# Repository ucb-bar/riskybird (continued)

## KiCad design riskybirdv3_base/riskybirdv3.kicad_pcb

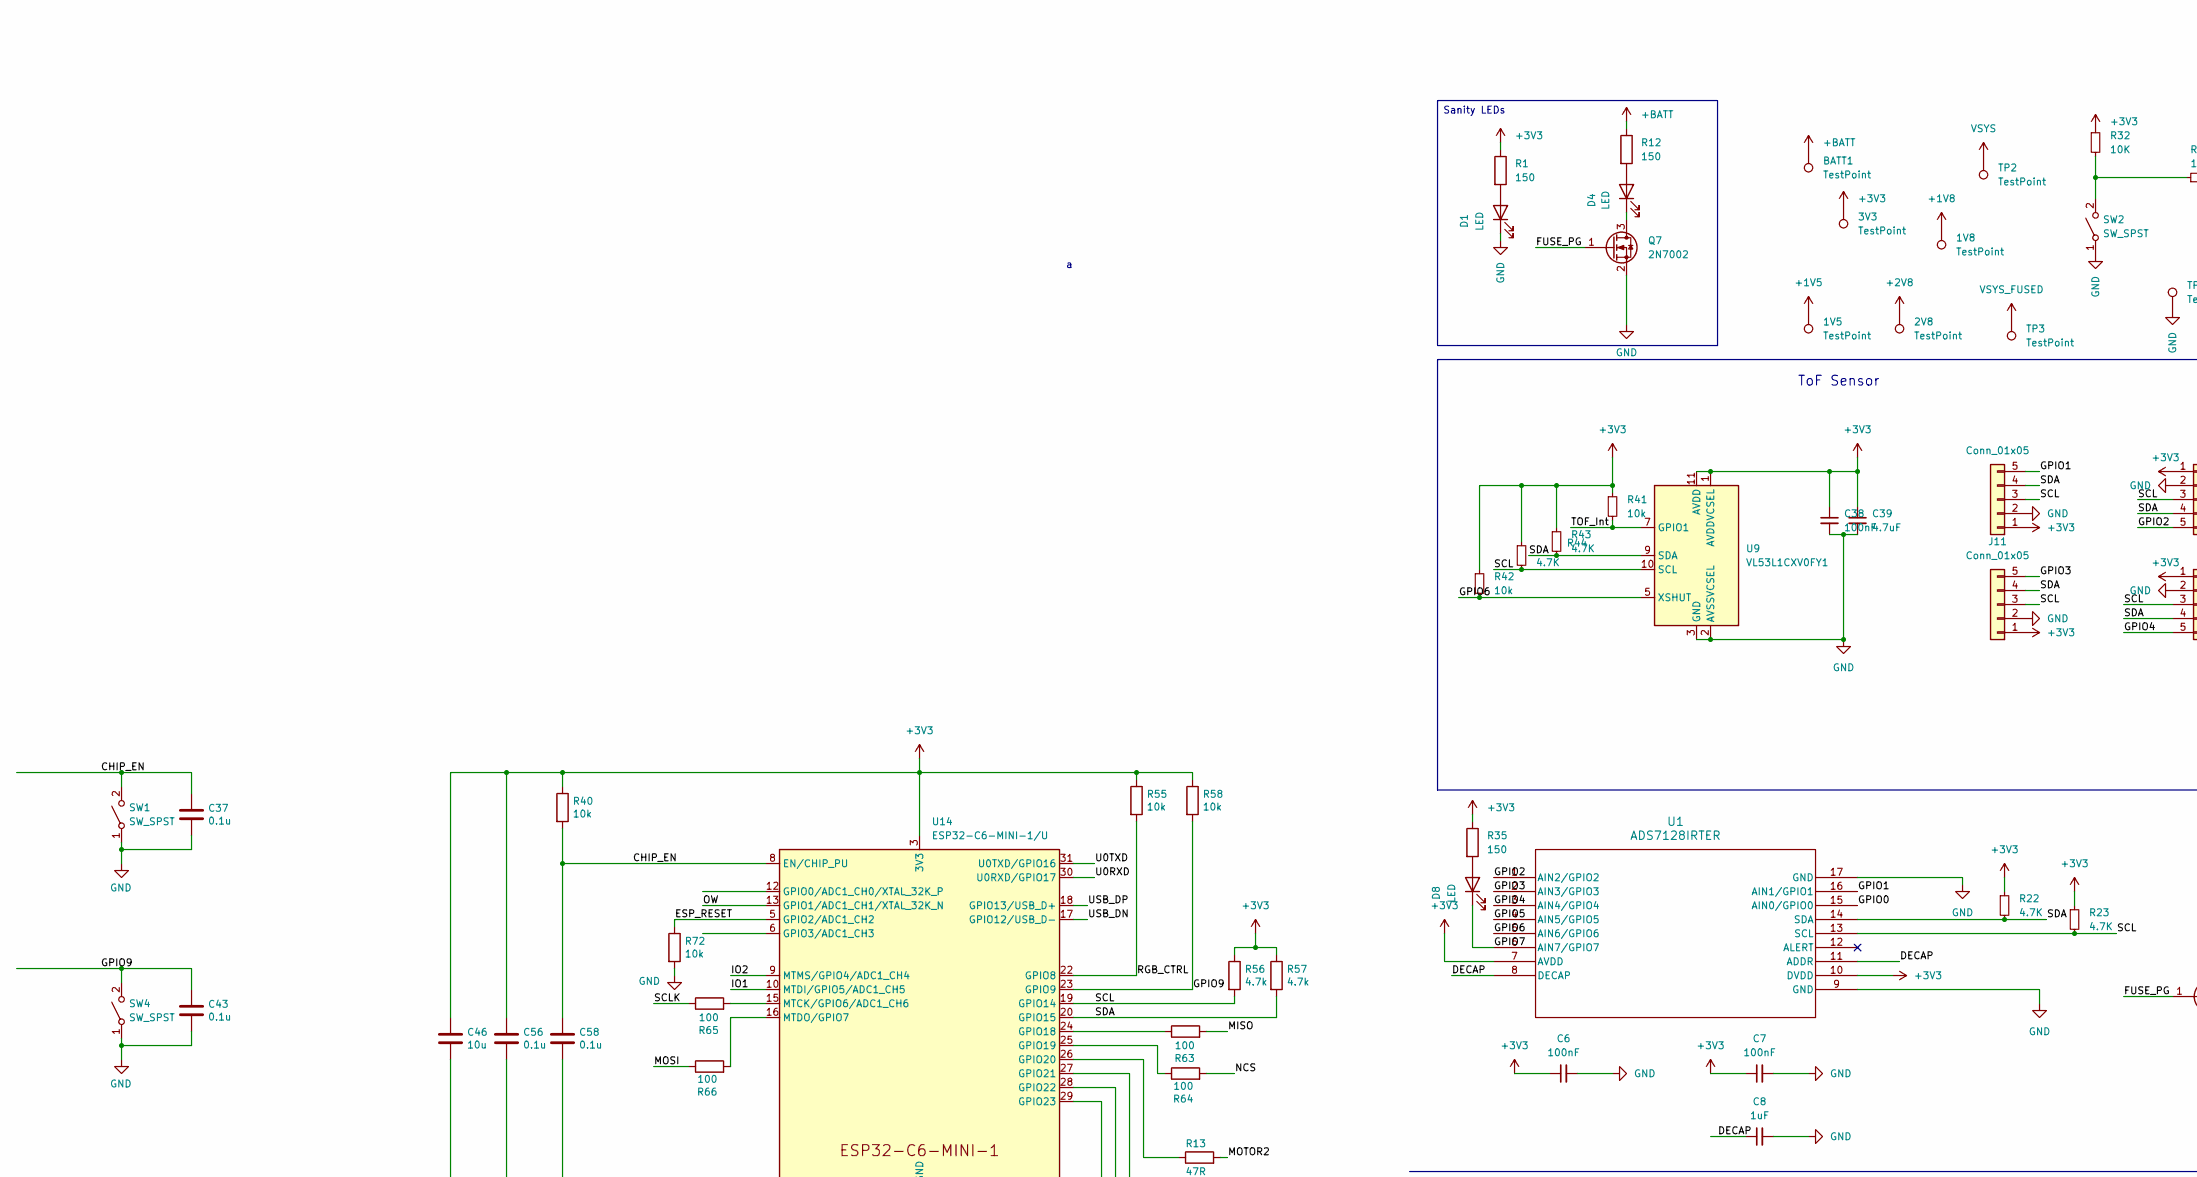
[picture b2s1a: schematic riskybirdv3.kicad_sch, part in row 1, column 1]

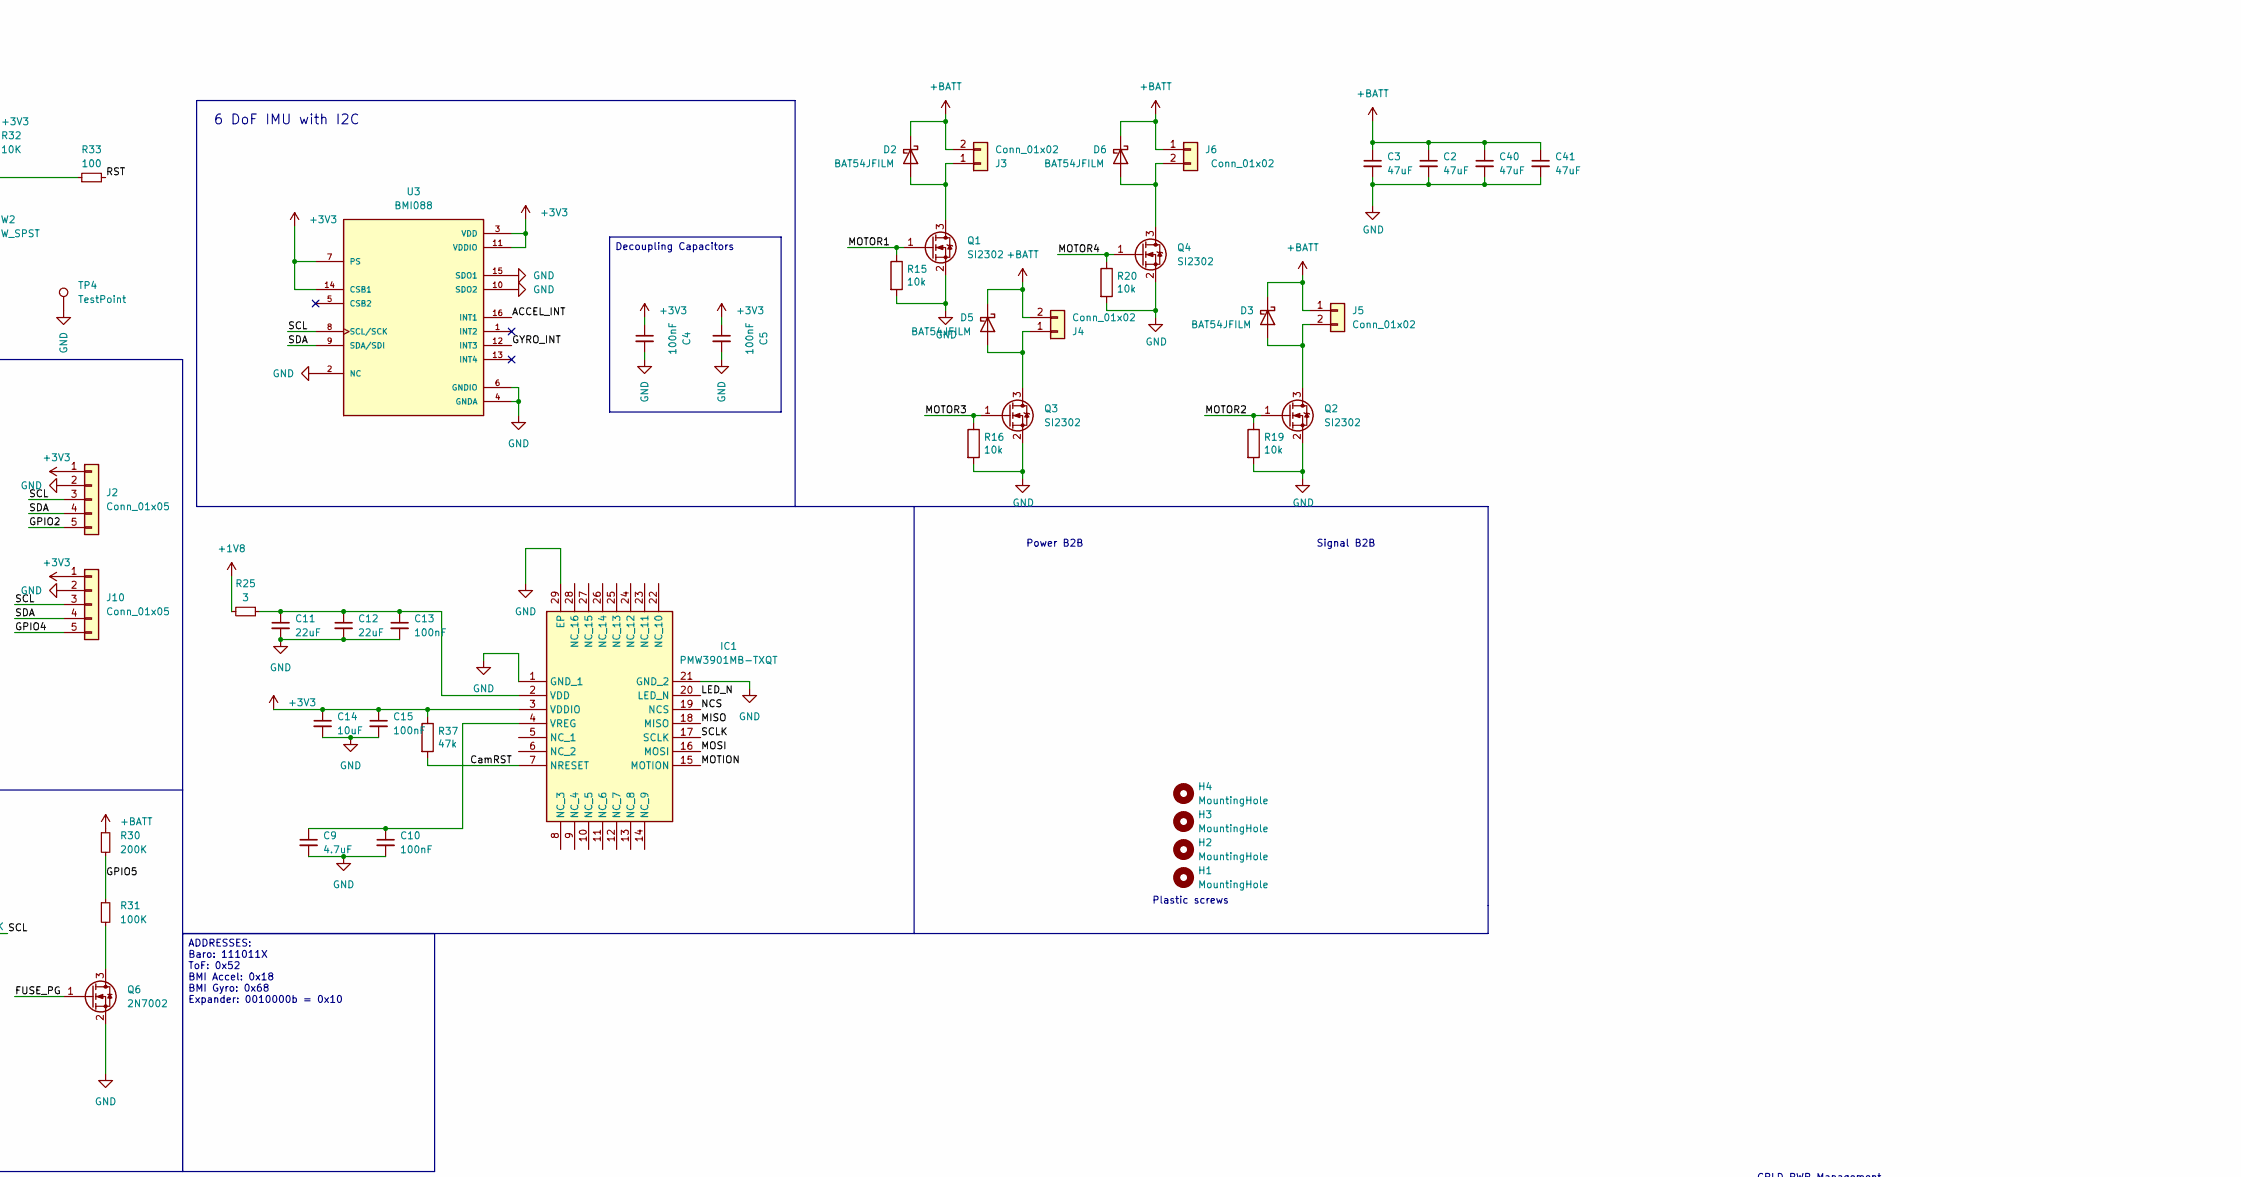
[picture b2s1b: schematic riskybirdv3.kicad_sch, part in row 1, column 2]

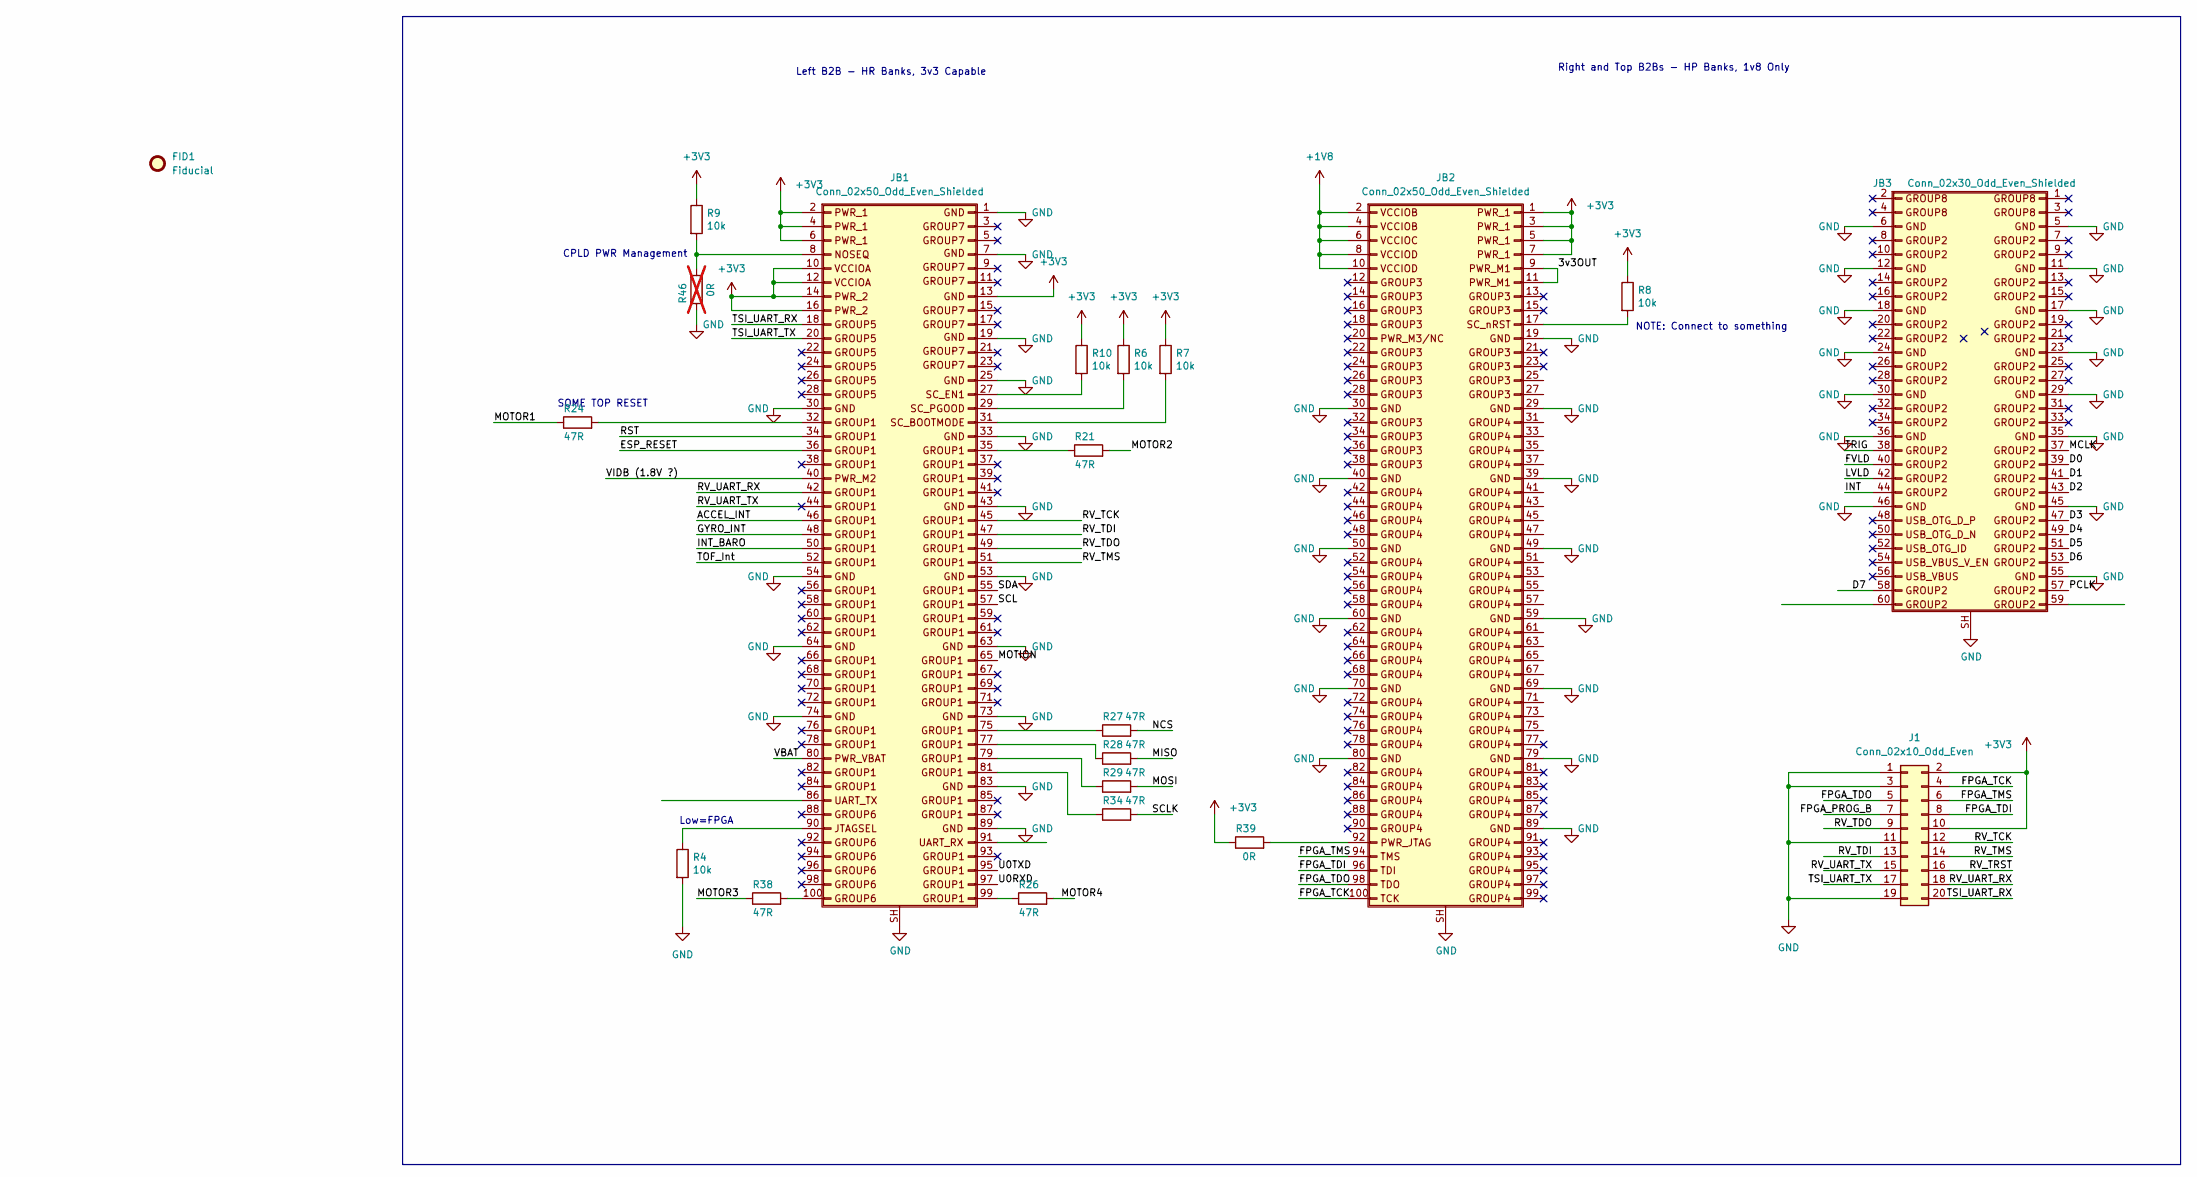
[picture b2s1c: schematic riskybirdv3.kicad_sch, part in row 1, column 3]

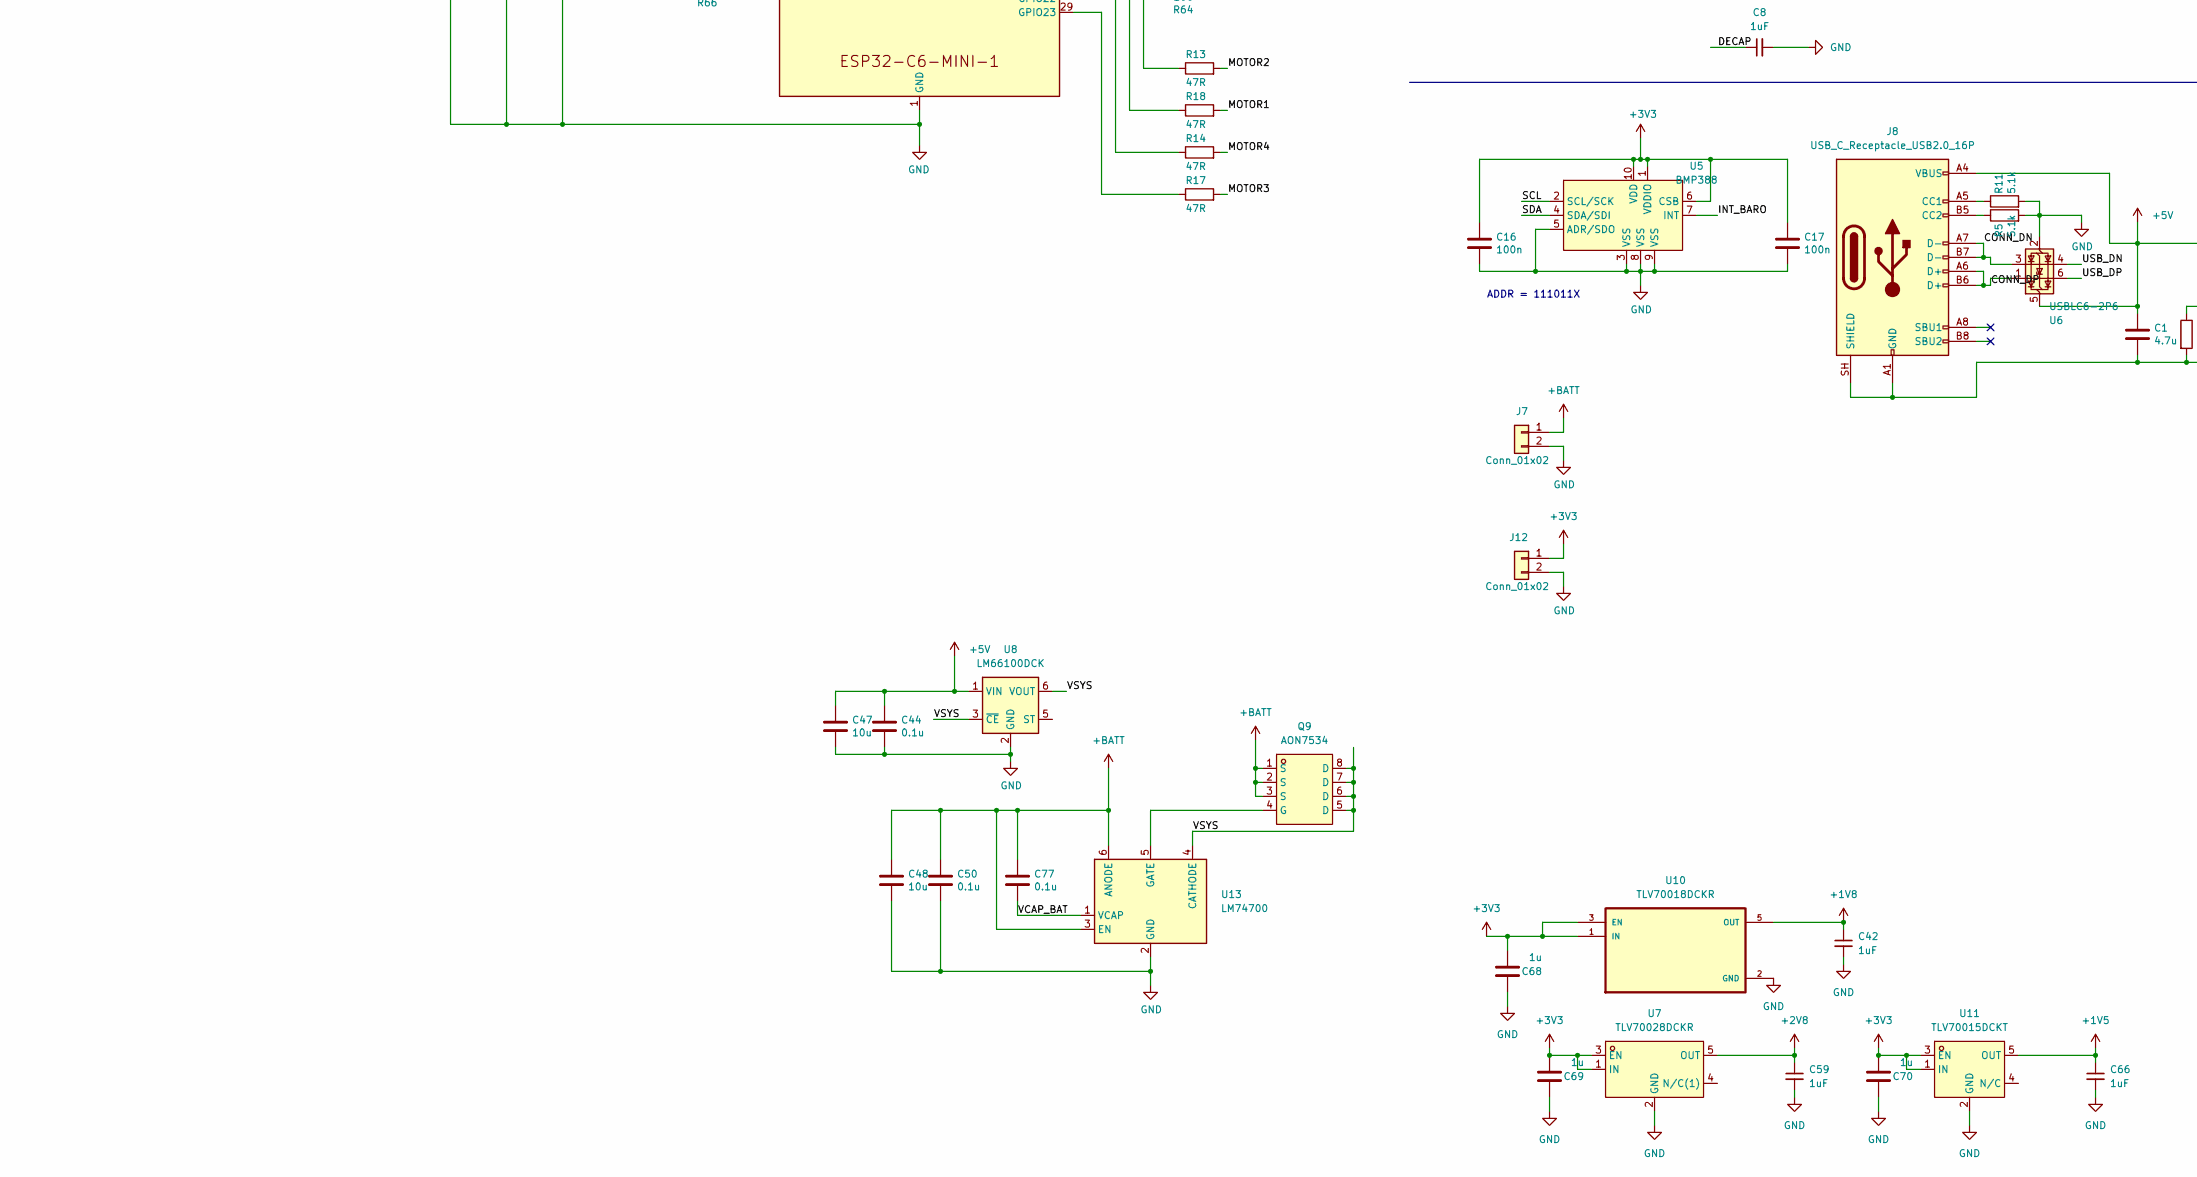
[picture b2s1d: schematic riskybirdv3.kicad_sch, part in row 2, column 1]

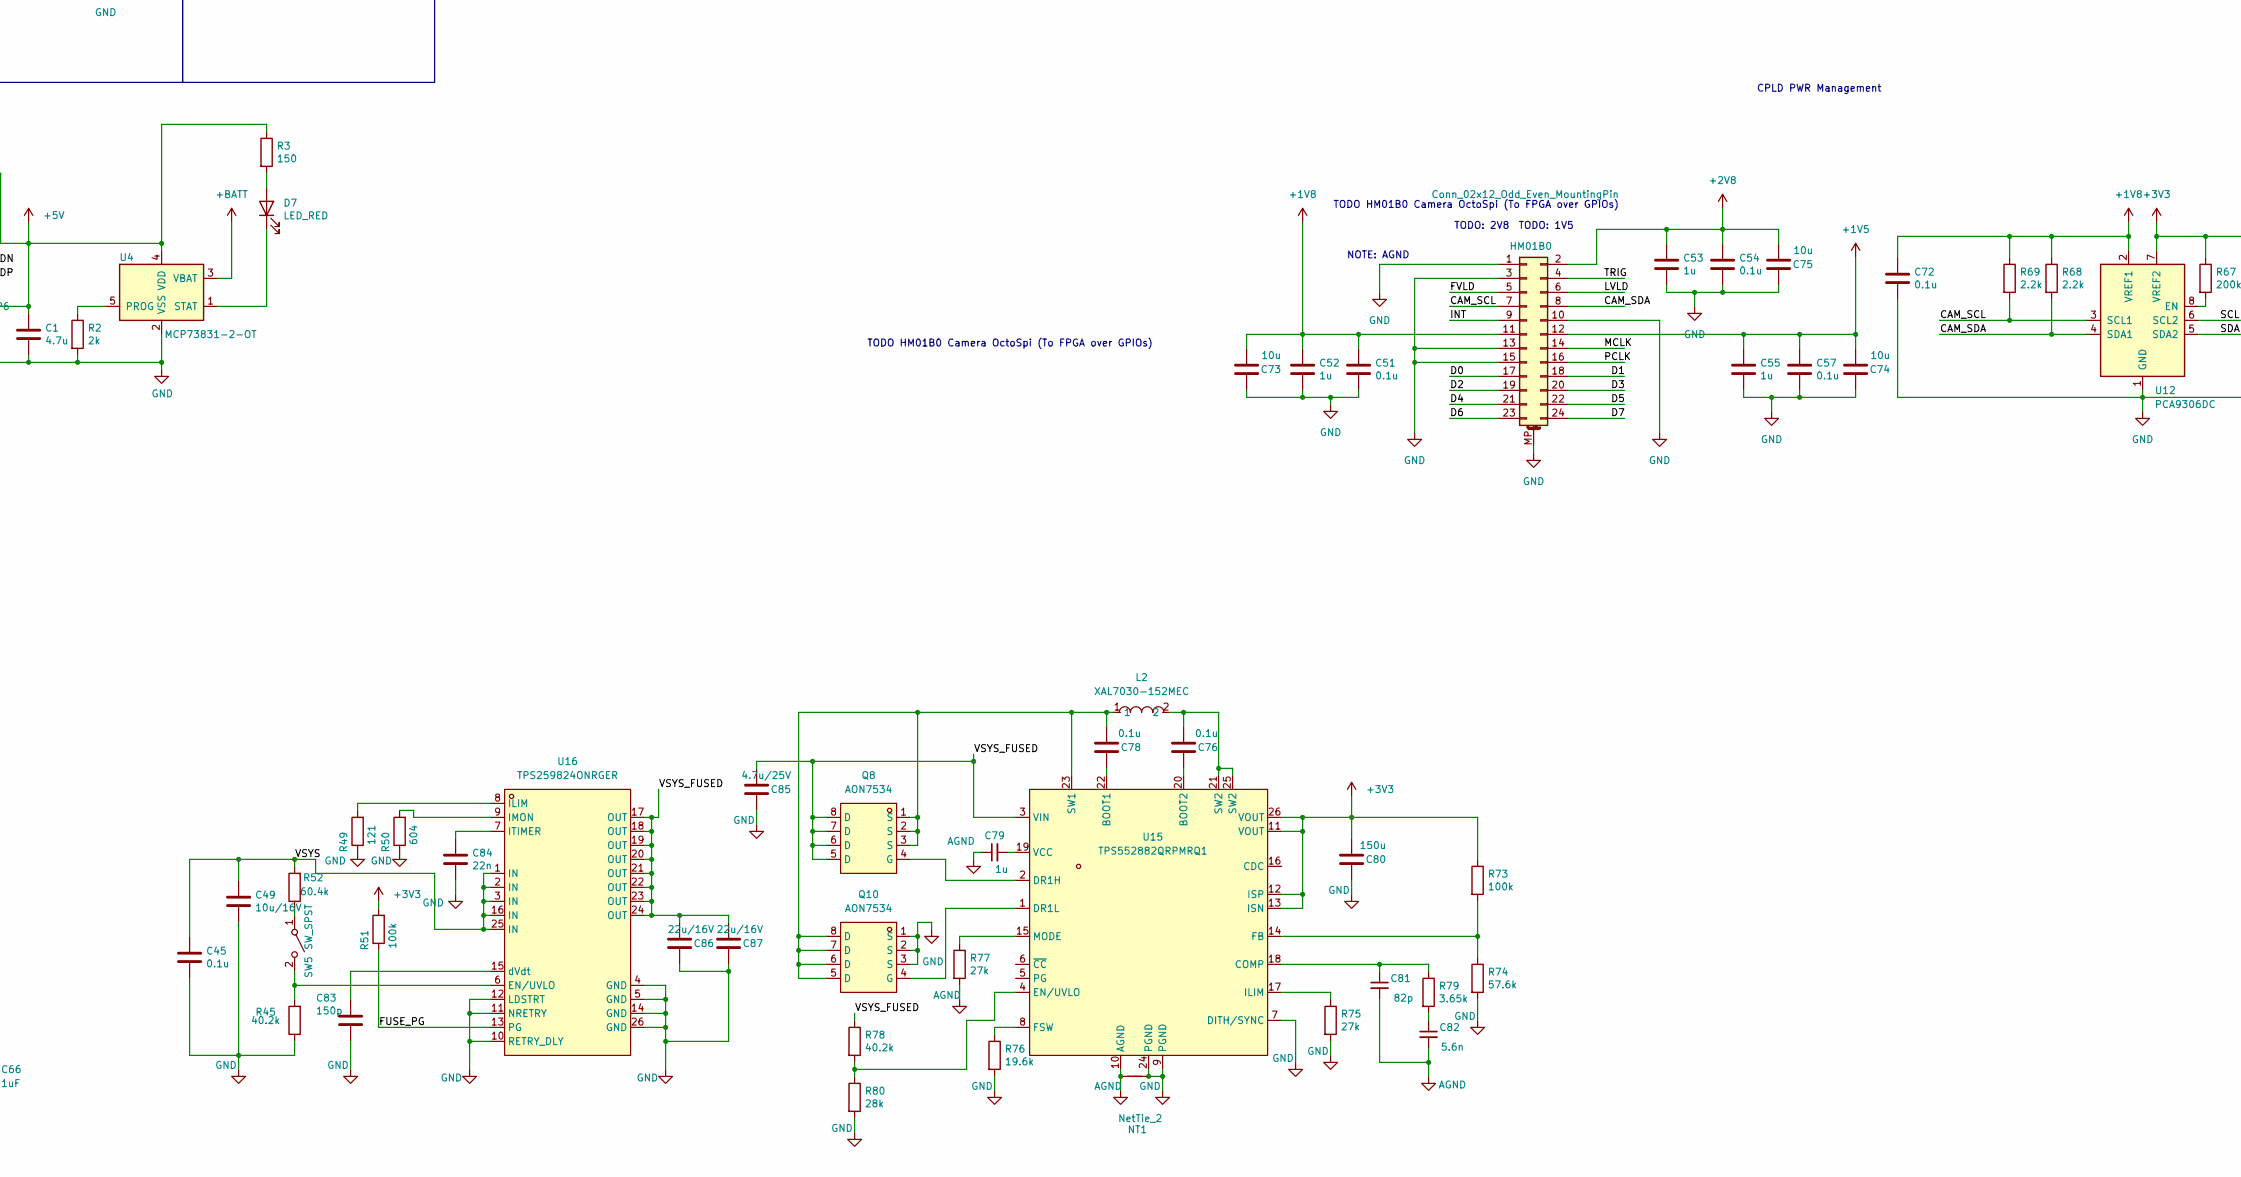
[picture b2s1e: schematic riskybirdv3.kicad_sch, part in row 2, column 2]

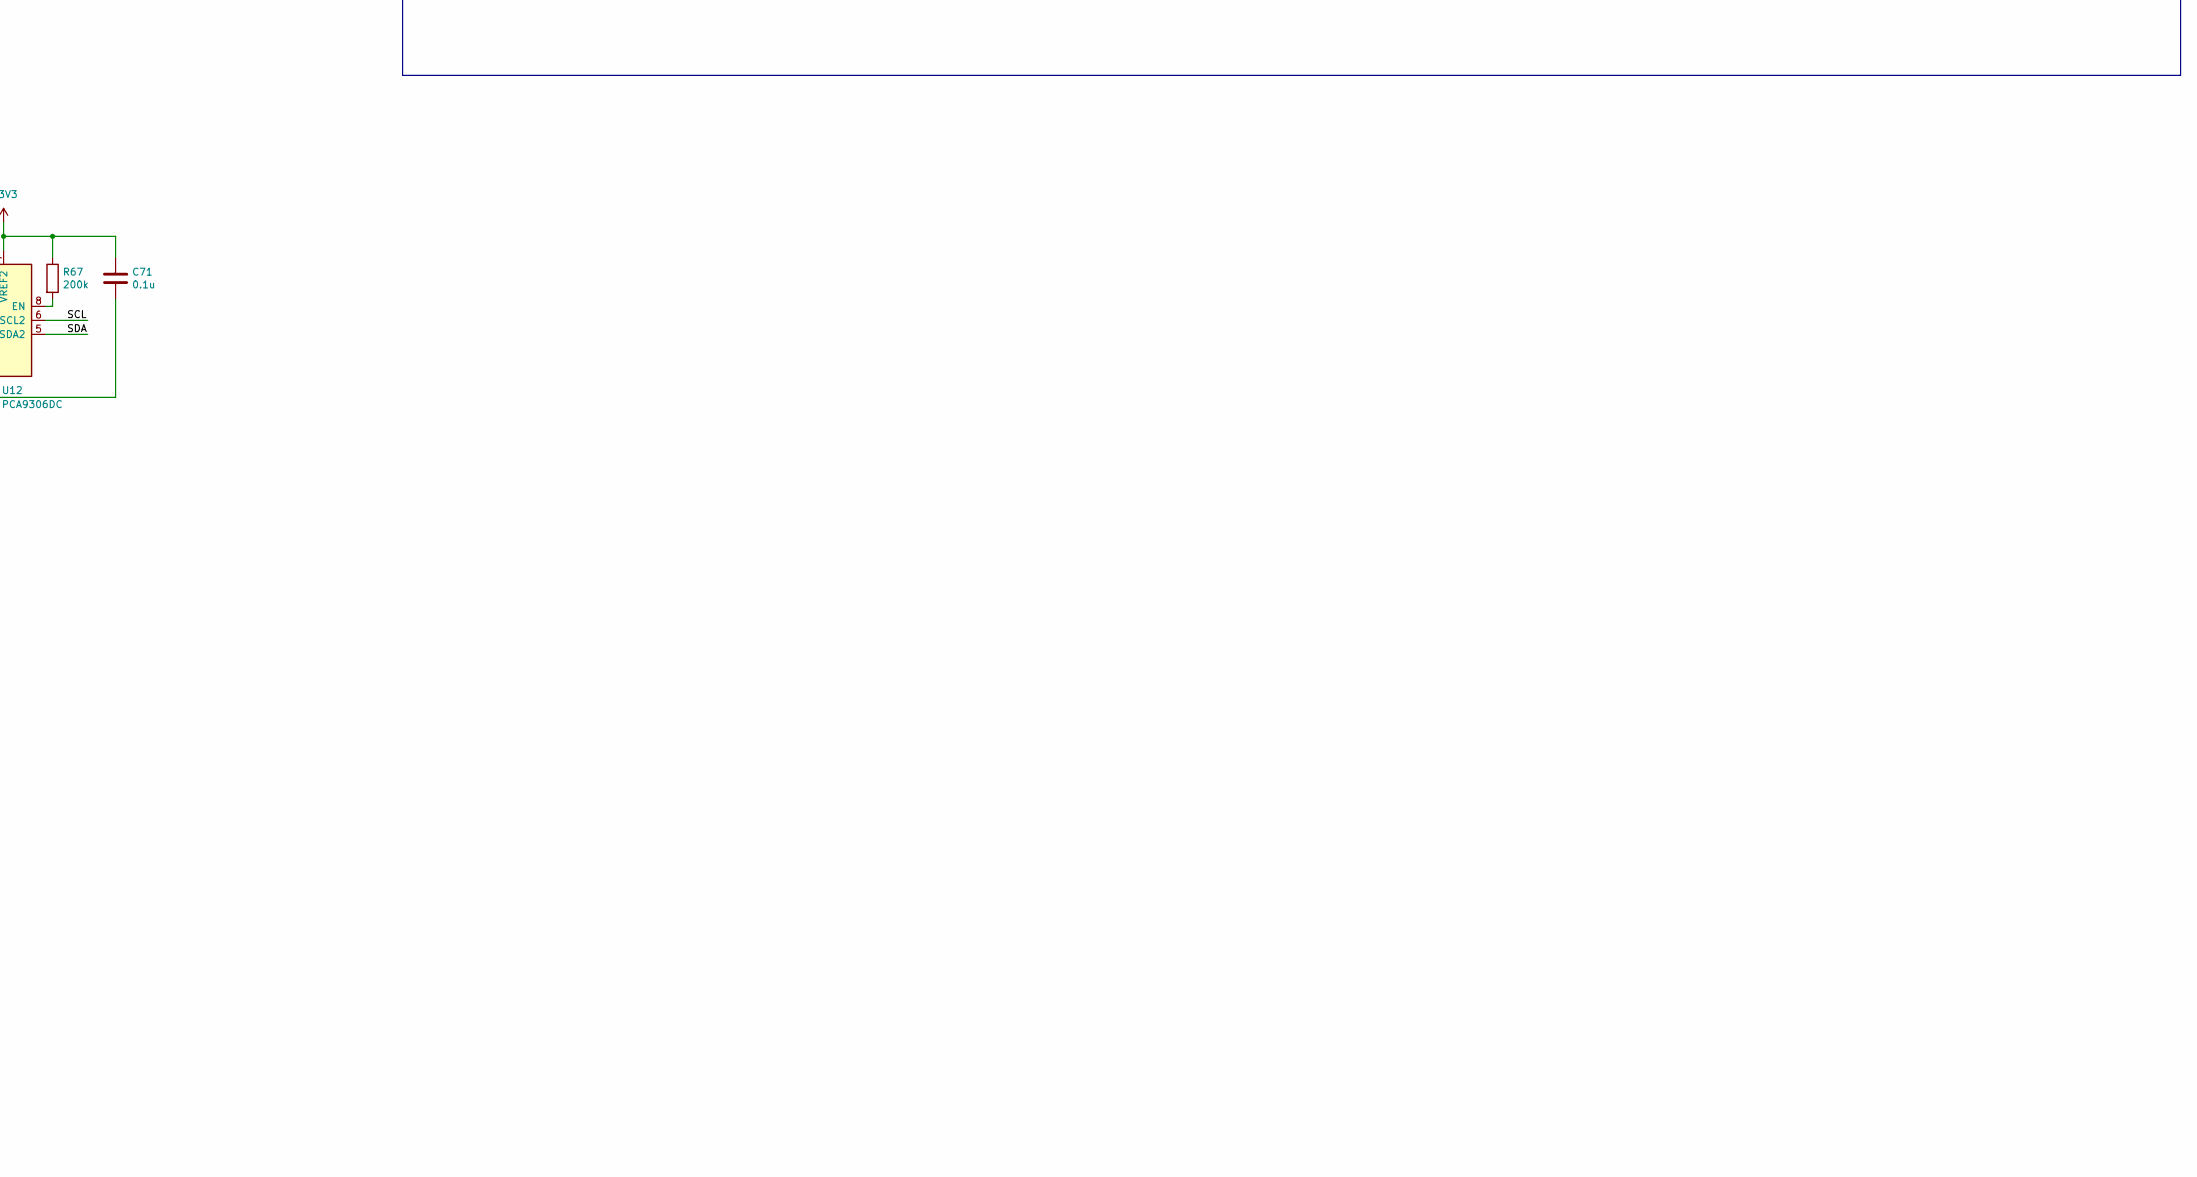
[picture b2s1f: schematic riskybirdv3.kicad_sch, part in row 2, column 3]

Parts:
1V5, 1V8, 2V8, 3V3: TestPoint; TestPoint_Pad_D1.0mm
BATT1: TestPoint; TestPoint_Pad_D1.0mm
C1: 4.7u; C_0201_0603Metric; MPN GRM035R60J475ME15D; LCSC Part C335103
C2, C3, C40, C41: 47uF; C_0603_1608Metric; LCSC Part C140782
C4, C5, C6, C7, C10, C13, C15, C38: 100nF; C_0201_0603Metric; MPN GRM033R60J104KE19D; LCSC Part C76928
C8, C42, C59, C66: 1uF; C_0201_0603Metric; MPN CL03A105MQ3CSNH; LCSC Part C53067
C9, C39: 4.7uF; C_0201_0603Metric; MPN GRM035R60J475ME15D; LCSC Part C335103
C11, C12: 22uF; C_0603_1608Metric; LCSC Part C59461
C14: 10uF; C_0402_1005Metric; LCSC Part C15525
C16, C17: 100n; C_0201_0603Metric; MPN GRM033R60J104KE19D; LCSC Part C76928
C37, C43, C44, C45, C50, C51, C54, C56, C57, C58, C76, C77, C78: 0.1u; C_0201_0603Metric; MPN GRM033R60J104KE19D; LCSC Part C76928
C46, C47, C48, C73, C74, C75: 10u; C_0402_1005Metric; LCSC Part C15525
C49: 10u/16V; C_0603_1608Metric; LCSC Part C962136
C52, C53, C55, C68, C69, C70, C79: 1u; C_0201_0603Metric; MPN CL03A105MQ3CSNH; LCSC Part C53067
C71, C72: 0.1u; C_0402_1005Metric; LCSC Part C1525
C80: 150u; C_1206_3216Metric; LCSC Part C528968
C81: 82p; C_0201_0603Metric; MPN GRM0335C1H820JA01D; LCSC Part C161439
C82: 5.6n; C_0201_0603Metric; MPN 0201B562K500NT; LCSC Part C3037635
C83: 150p; C_0201_0603Metric; MPN GRM0335C1H151FA01D; LCSC Part C384963
C84: 22n; C_0201_0603Metric; MPN EMK063B7223KP-F; LCSC Part C2880350
C85: 4.7u/25V; C_0402_1005Metric; LCSC Part C2858031
C86, C87: 22u/16V; C_0603_1608Metric; LCSC Part C6119868
D1, D4, D8: LED; LED_0402_1005Metric; LCSC Part C965793
D2, D3, D5, D6: BAT54JFILM; D_SOD-323_HandSoldering; LCSC Part C86299
D7: LED_RED; LED_0402_1005Metric; LCSC Part C25503345
FID1: Fiducial
H1, H2, H3, H4: MountingHole; MountingHole_2.2mm_M2
HM01B0: Conn_02x12_Odd_Even_MountingPin; CONN-SMD_24P-P0.40_5055502420-HM01B0; MPN 505550-2420; LCSC Part C3642262
IC1: PMW3901MB-TXQT; PMW3901MBTXQT; Manufacturer_Part_Number PMW3901MB-TXQT; LCSC Part C43496881
J1: Conn_02x10_Odd_Even; CONN-SMD_FTSH-110-01-L-DV-K-TR; MPN FTSH-110-01-L-DV-K-TR; LCSC Part C20728453
J2, J9, J10, J11: Conn_01x05; PinHeader_1x05_P2.54mm_Vertical
J3, J4, J5, J6: Conn_01x02; Molex_PicoBlade_53048-0210_1x02_P1.25mm_Horizontal; MPN 53048-0210; LCSC Part C505099
J7, J12: Conn_01x02; PinHeader_1x02_P2.00mm_Vertical
J8: USB_C_Receptacle_USB2.0_16P; USB_C_Receptacle_HRO_TYPE-C-31-M-12; MPN TYPE-C-31-M-12; LCSC Part C165948
JB1, JB2: Conn_02x50_Odd_Even_Shielded; Samtec_LSHM-150-xx.x-x-DV-S_2x50-1SH_P0.50mm_Vertical; MPN LSHM-150-04.0-L-DV-A-S-K-TR; LCSC Part C5367357
JB3: Conn_02x30_Odd_Even_Shielded; Samtec_LSHM-130-xx.x-x-DV-S_2x30-1SH_P0.50mm_Vertical; MPN LSHM-130-04.0-L-DV-A-S-K-TR; LCSC Part C3645597
L2: XAL7030-152MEC; IND-SMD_L7.5-W7.5_XAL7030-152MEC; MPN XAL7030-152MEC; LCSC Part C5352784
NT1: NetTie_2; NetTie-2_SMD_Pad0.5mm
Q1, Q2, Q3, Q4: SI2302; SOT-23; LCSC Part C2891732
Q6, Q7: 2N7002; SOT-23; LCSC Part C8545
Q8, Q9, Q10: AON7534; PQFN-8_L3.1-W3.1-P0.65-LS3.3-BL; MPN AON7534; LCSC Part C115844
R1, R3, R12, R35: 150; R_0201_0603Metric; MPN RC0201FR-07150RL; LCSC Part C295773
R2: 2k; R_0201_0603Metric; MPN 0201WMF2001TEE; LCSC Part C270358
R4, R6, R7, R8, R9, R10, R15, R16, R19, R20, R40, R41, R42, R55, R58, R72: 10k; R_0201_0603Metric; MPN 0201WMF1002TEE; LCSC Part C473048
R5, R11: 5.1k; R_0201_0603Metric; MPN 0201WMF5101TEE; LCSC Part C270344
R13, R14, R17, R18, R21, R24, R26, R27, R28, R29, R34, R38: 47R; R_0201_0603Metric; MPN RC0201FR-0747RL; LCSC Part C273279
R22, R23, R43, R44: 4.7K; R_0201_0603Metric; MPN 0201WMF4701TEE; LCSC Part C270346
R25: 3; R_0603_1608Metric; LCSC Part C22356394
R30: 200K; R_0201_0603Metric; MPN RC0201FR-07200KL; LCSC Part C138163
R31: 100K; R_0201_0603Metric; MPN 0201WMF1003TEE; LCSC Part C270364
R32: 10K; R_0201_0603Metric; MPN 0201WMF1002TEE; LCSC Part C473048
R33, R63, R64, R65, R66: 100; R_0201_0603Metric; MPN RC0201FR-07100RL; LCSC Part C77623
R37: 47k; R_0201_0603Metric; MPN 0201WMF4702TEE; LCSC Part C270345
R39: 0R; R_0201_0603Metric; MPN RC0201FR-070RL; LCSC Part C106227
R45, R78: 40.2k; R_0201_0603Metric; MPN 0201WMF4022TEE; LCSC Part C423536
R46: 0R; R_0201_0603Metric; MPN RC0201FR-070RL; LCSC Part C106227; not fitted
R49: 121; R_0201_0603Metric; MPN RC0201FR-07121RL; LCSC Part C474519
R50: 604; R_0201_0603Metric; LCSC Part C423470
R51, R73: 100k; R_0201_0603Metric; MPN 0201WMF1003TEE; LCSC Part C270364
R52: 60.4k; R_0201_0603Metric; LCSC Part C473653
R56, R57: 4.7k; R_0201_0603Metric; MPN 0201WMF4701TEE; LCSC Part C270346
R67: 200k; R_0201_0603Metric; MPN RC0201FR-07200KL; LCSC Part C138163
R68, R69: 2.2k; R_0201_0603Metric; MPN 0201WMF2201TEE; LCSC Part C473508
R74: 57.6k; R_0201_0603Metric; MPN RC-01W5762FT; LCSC Part C320974
R75, R77: 27k; R_0201_0603Metric; MPN RC0201FR-0727KL; LCSC Part C273283
R76: 19.6k; R_0201_0603Metric; MPN 0201WMF1962TEE; LCSC Part C423675
R79: 3.65k; R_0201_0603Metric; MPN RTT013651FTH; LCSC Part C166220
R80: 28k; R_0201_0603Metric; MPN 0201WMF2802TEE; LCSC Part C473489
SW1, SW2, SW4: SW_SPST; SW_SPST_B3U-1000P; MPN B3U-1000P; LCSC Part C231329
SW5: SW_SPST; SW-SMD_MSK12CO2; MPN MSK12C02; LCSC Part C2681570
TP2, TP3, TP4: TestPoint; TestPoint_Pad_D1.0mm
U1: ADS7128IRTER; WQFN-16-1EP_3x3mm_P0.5mm_EP1.6x1.6mm; LCSC Part C2867992
U3: BMI088; Bosch_LGA-16_4.5x3mm_P0.5mm_LayoutBorder7x1y_ClockwisePinNu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; LCSC Part C194919
U4: MCP73831-2-OT; SOT-23-5; MPN MCP73831T-2ACI/OT; LCSC Part C424093
U5: BMP388; BMP390; MPN BMP388; LCSC Part C779278
U6: USBLC6-2P6; SOT-666; LCSC Part C2827693
U7: TLV70028DCKR; SC-70-5_L2.1-W1.3-P0.65-LS2.1-BL; MPN TLV70028DCKR; LCSC Part C398921
U8: LM66100DCK; SOT-363_SC-70-6; LCSC Part C5219211
U9: VL53L1CXV0FY1; ST_VL53L1x; LCSC Part C190004
U10: TLV70018DCKR; SOT-353_SC-70-5; LCSC Part C133796
U11: TLV70015DCKT; SC-70-5_L2.0-W1.3-P0.65-LS2.1-BR; MPN TLV70015DCKT; LCSC Part C2878901
U12: PCA9306DC; VSSOP-8_2.3x2mm_P0.5mm; LCSC Part C33196
U13: LM74700; SOT-23-6; LCSC Part C2941042
U14: ESP32-C6-MINI-1/U; ESP32-C6-MINI-1U; MPN ESP32-C6-MINI-1U-H4; LCSC Part C20627095
U15: TPS552882QRPMRQ1; VQFN-HR-26_L4.0-W3.5_TPS55288RPMR; MPN TPS552882QRPMRQ1; LCSC Part C2876594
U16: TPS259824ONRGER; VQFN-24_L4.0-W4.0-P0.50-TL-EP_TI_RGE; MPN TPS259824ONRGER; LCSC Part C2155766

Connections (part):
+1V5: 1V5.1 (1_1), C55.1, C57.1, C66.1, C74.2, HM01B0.12, U11.5 (OUT)
+1V8: 1V8.1 (1_1), C42.1, C51.1, C52.1, C72.1, C73.2, HM01B0.11, JB2.2, JB2.4, JB2.6, JB2.8, JB2.10, R25.2, R68.1, R69.1, U10.5 (OUT), U12.2 (VREF1)
+2V8: 2V8.1 (1_1), C53.1, C54.1, C59.1, C75.2, HM01B0.2, U7.5 (OUT)
+3V3: 3V3.1 (1_1), C4.1, C5.1, C6.1, C7.1, C14.1, C15.1, C16.1, C17.1, C38.1, C39.1, C46.1, C56.1, C68.2, C69.2, C70.2, C71.1, C80.2, IC1.3 (VDDIO), J1.2, J1.10, J2.1, J9.1, J10.1, J11.1, J12.1, JB1.2, JB1.4, JB1.6, JB1.10, JB1.12, JB1.13, JB1.14, JB1.16, JB2.1, JB2.3, JB2.5, JB2.7, R1.1, R6.1, R7.1, R8.1, R9.1, R10.1, R22.1, R23.1, R32.1, R35.1, R37.1, R39.1, R40.1, R41.1, R42.1, R43.1, R44.1, R51.2, R55.1, R56.1, R57.1, R58.1, R67.1, R73.1, U1.7 (AVDD), U1.10 (DVDD), U3.3 (VDD), U3.7 (PS), U3.11 (VDDIO), U3.14 (CSB1), U5.1 (VDDIO), U5.6 (CSB), U5.10 (VDD), U7.1 (IN), U7.3 (EN), U9.1 (AVDDVCSEL), U9.11 (AVDD), U10.1 (IN), U10.3 (EN), U11.1 (IN), U11.3 (EN), U12.7 (VREF2), U14.3 (3V3)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
+5V: C1.1, C44.1, C47.1, J8.A4 (VBUS), J8.A9 (VBUS), J8.B4 (VBUS), J8.B9 (VBUS), R3.1, U4.4 (VDD), U6.5 (VBUS), U8.1 (VIN)
+BATT: BATT1.1 (1_1), C2.1, C3.1, C40.1, C41.1, C48.1, C50.1, C77.1, D2.1 (K), D3.1 (K), D5.1 (K), D6.1 (K), J3.2, J4.2, J5.1, J6.1, J7.1, Q9.1 (S), Q9.2 (S), Q9.3 (S), R12.1, R30.1, U4.3 (VBAT), U13.3 (EN), U13.6 (ANODE)
/3v3OUT: JB2.9, JB2.11
/ACCEL_INT: JB1.46, U3.16 (INT1)
/CAM_SCL: HM01B0.7, R69.2, U12.3 (SCL1)
/CAM_SDA: HM01B0.8, R68.2, U12.4 (SDA1)
/CHIP_EN: C37.1, C58.1, R40.2, SW1.2 (B), U14.8 (EN/CHIP_PU)
/CONN_DN: J8.A7 (D-), J8.B7 (D-), U6.3 (I/O2)
/CONN_DP: J8.A6 (D+), J8.B6 (D+), U6.1 (I/O1)
/CamRST: IC1.7 (NRESET), R37.2
/D0: HM01B0.17, JB3.39
/D1: HM01B0.18, JB3.41
/D2: HM01B0.19, JB3.43
/D3: HM01B0.20, JB3.47
/D4: HM01B0.21, JB3.49
/D5: HM01B0.22, JB3.51
/D6: HM01B0.23, JB3.53
/D7: HM01B0.24, JB3.58
/DECAP: C8.1, U1.8 (DECAP), U1.11 (ADDR)
/ESP_RESET: JB1.36, R72.1, U14.5 (GPIO2/ADC1_CH2)
/FPGA_PROG_B: J1.7
/FPGA_TCK: J1.4, JB2.100 (Pin_80)
/FPGA_TDI: J1.8, JB2.96 (Pin_76)
/FPGA_TDO: J1.5, JB2.98 (Pin_78)
/FPGA_TMS: J1.6, JB2.94 (Pin_74)
/FUSE_PG: Q6.1 (G), Q7.1 (G), R51.1, U16.13 (PG)
/FVLD: HM01B0.5, JB3.40
/GPIO0: U1.15 (AIN0/GPIO0)
/GPIO1: J9.5, U1.16 (AIN1/GPIO1)
/GPIO2: J2.5, U1.1 (AIN2/GPIO2)
/GPIO3: J11.5, U1.2 (AIN3/GPIO3)
/GPIO4: J10.5, U1.3 (AIN4/GPIO4)
/GPIO5: R30.2, R31.1, U1.4 (AIN5/GPIO5)
/GPIO6: R42.2, U1.5 (AIN6/GPIO6), U9.5 (XSHUT)
/GPIO7: D8.1 (K), U1.6 (AIN7/GPIO7)
/GPIO9: C43.1, R58.2, SW4.2 (B), U14.23 (GPIO9)
/GYRO_INT: JB1.48, U3.12 (INT3)
/INT: HM01B0.9, JB3.44
/INT_BARO: JB1.50, U5.7 (INT)
/IO1: U14.10 (MTDI/GPIO5/ADC1_CH5)
/IO2: U14.9 (MTMS/GPIO4/ADC1_CH4)
/LED_N: IC1.20 (LED_N)
/LVLD: HM01B0.6, JB3.42
/MCLK: HM01B0.14, JB3.37
/MISO: IC1.18 (MISO), R28.2, R63.2
/MOSI: IC1.16 (MOSI), R29.2, R66.1
/MOTION: IC1.15 (MOTION), JB1.65
/MOTOR1: Q1.1 (G), R15.1, R18.2, R24.1
/MOTOR2: Q2.1 (G), R13.2, R19.1, R21.2
/MOTOR3: Q3.1 (G), R16.1, R17.2, R38.1
/MOTOR4: Q4.1 (G), R14.2, R20.1, R26.2
/NCS: IC1.19 (NCS), R27.2, R64.2
/OW: U14.13 (GPIO1/ADC1_CH1/XTAL_32K_N)
/PCLK: HM01B0.16, JB3.57
/RGB_CTRL: R55.2, U14.22 (GPIO8)
/RST: JB1.34, R33.2
/RV_TCK: J1.12, JB1.45
/RV_TDI: J1.13, JB1.47
/RV_TDO: J1.9, JB1.49
/RV_TMS: J1.14, JB1.51
/RV_TRST: J1.16
/RV_UART_RX: J1.18, JB1.42
/RV_UART_TX: J1.15, JB1.44
/SCL: J2.3, J9.3, J10.3, J11.3, JB1.57, R23.2, R44.2, R56.2, U1.13 (SCL), U3.8 (SCL/SCK), U5.2 (SCL/SCK), U9.10 (SCL), U12.6 (SCL2), U14.19 (GPIO14)
/SCLK: IC1.17 (SCLK), R34.2, R65.1
/SDA: J2.4, J9.4, J10.4, J11.4, JB1.55, R22.2, R43.2, R57.2, U1.14 (SDA), U3.9 (SDA/SDI), U5.4 (SDA/SDI), U9.9 (SDA), U12.5 (SDA2), U14.20 (GPIO15)
/TOF_Int: JB1.52, R41.2, U9.7 (GPIO1)
/TRIG: HM01B0.4, JB3.38
/TSI_UART_RX: J1.20, JB1.18
/TSI_UART_TX: J1.17, JB1.20
/U0RXD: JB1.97 (Pin_77), U14.30 (U0RXD/GPIO17)
/U0TXD: JB1.95 (Pin_75), U14.31 (U0TXD/GPIO16)
/USB_DN: U6.4 (I/O2), U14.17 (GPIO12/USB_D-)
/USB_DP: U6.6 (I/O1), U14.18 (GPIO13/USB_D+)
/VBAT: JB1.80
/VCAP_BAT: C77.2, U13.1 (VCAP)
/VIDB (1.8V ?): JB1.40
AGND: C79.1, C81.2, C82.2, NT1.1, R77.2, U15.10 (AGND)
GND: C1.2, C2.2, C3.2, C4.2, C5.2, C6.2, C7.2, C8.2, C9.2, C10.2, C11.2, C12.2, C13.2, C14.2, C15.2, C16.2, C17.2, C37.2, C38.2, C39.2, C40.2, C41.2, C42.2, C43.2, C44.2, C45.2, C46.2, C47.2, C48.2, C49.2, C50.2, C51.2, C52.2, C53.2, C54.2, C55.2, C56.2, C57.2, C58.2, C59.2, C66.2, C68.1, C69.1, C70.1, C71.2, C72.2, C73.1, C74.1, C75.1, C80.1, C83.2, C84.2, C85.1, C86.1, C87.1, D1.1 (K), HM01B0.1, HM01B0.3, HM01B0.10, HM01B0.13, HM01B0.15, HM01B0.MP (MountPin), IC1.1 (GND_1), IC1.21 (GND_2), IC1.29 (EP), J1.1, J1.3, J1.11, J1.19, J2.2, J7.2, J8.A1 (GND), J8.A12 (GND), J8.B1 (GND), J8.B12 (GND), J8.SH (SHIELD), J9.2, J10.2, J11.2, J12.2, JB1.1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
unnamed: C76.2, L2.2, U15.21 (SW2), U15.25 (SW2)
unnamed: C82.1, R79.2
unnamed: D1.2 (A), R1.2
unnamed: D2.2 (A), J3.1, Q1.3 (D)
unnamed: D3.2 (A), J5.2, Q2.3 (D)
unnamed: D4.2 (A), R12.2
unnamed: D4.1 (K), Q7.3 (D)
unnamed: D5.2 (A), J4.1, Q3.3 (D)
unnamed: D6.2 (A), J6.2, Q4.3 (D)
unnamed: D7.2 (A), R3.2
unnamed: D7.1 (K), U4.1 (STAT)
unnamed: D8.2 (A), R35.2
unnamed: C11.1, C12.1, C13.1, IC1.2 (VDD), R25.1
unnamed: C9.1, C10.1, IC1.4 (VREG)
unnamed: J8.A5 (CC1), R11.1
unnamed: J8.B5 (CC2), R5.1
unnamed: JB1.8, R9.2, R46.2
unnamed: JB1.27, R10.2
unnamed: JB1.29, R6.2
unnamed: JB1.31, R7.2
unnamed: JB1.32, R24.2
unnamed: JB1.35, R21.1
unnamed: JB1.81 (Pin_61), R34.1
unnamed: JB1.90 (Pin_70), R4.1
unnamed: JB1.75, R27.1
unnamed: JB1.77, R28.1
unnamed: JB1.79, R29.1
unnamed: JB1.99 (Pin_79), R26.1
unnamed: JB1.100 (Pin_80), R38.2
unnamed: JB2.17, R8.2
unnamed: JB2.92 (Pin_72), R39.2
unnamed: Q6.3 (D), R31.2
unnamed: Q8.4 (G), U15.2 (DR1H)
unnamed: Q9.4 (G), U13.5 (GATE)
unnamed: Q10.4 (G), U15.1 (DR1L)
unnamed: R32.2, R33.1, SW2.2 (B)
unnamed: R52.1, SW5.1 (A)
unnamed: R45.2, SW5.2 (B), U16.6 (EN/UVLO)
unnamed: R2.1, U4.5 (PROG)
unnamed: R67.2, U12.8 (EN)
unnamed: R63.1, U14.24 (GPIO18)
unnamed: R64.1, U14.25 (GPIO19)
unnamed: R13.1, U14.26 (GPIO20)
unnamed: R18.1, U14.27 (GPIO21)
unnamed: R14.1, U14.28 (GPIO22)
unnamed: R17.1, U14.29 (GPIO23)
unnamed: R65.2, U14.15 (MTCK/GPIO6/ADC1_CH6)
unnamed: R66.2, U14.16 (MTDO/GPIO7)
unnamed: C78.1, U15.22 (BOOT1)
unnamed: C76.1, U15.20 (BOOT2)
unnamed: C81.1, R79.1, U15.18 (COMP)
unnamed: R78.2, R80.1, U15.4 (EN/UVLO)
unnamed: R73.2, R74.1, U15.14 (FB)
unnamed: R76.1, U15.8 (FSW)
unnamed: R75.1, U15.17 (ILIM)
unnamed: R77.1, U15.15 (MODE)
unnamed: C78.2, L2.1, Q8.1 (S), Q8.2 (S), Q8.3 (S), Q10.5 (D), Q10.6 (D), Q10.7 (D), Q10.8 (D), U15.23 (SW1)
unnamed: C79.2, U15.19 (VCC)
unnamed: R49.2, U16.8 (ILIM)
unnamed: R50.2, U16.9 (IMON)
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
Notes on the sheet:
Plastic screws
Power B2B
CPLD PWR Management
ToF Sensor
ADDR = 111011X
Low=FPGA
6 DoF IMU with I2C
TODO: 1V5
TODO: 2V8
Left B2B - HR Banks, 3v3 Capable
TODO HM01B0 Camera OctoSpi (To FPGA over GPIOs)
Right and Top B2Bs - HP Banks, 1v8 Only
NOTE: Connect to something
NOTE: AGND
SOME TOP RESET
Signal B2B
ADDRESSES: Baro: 111011X ToF: 0x52 BMI Accel: 0x18 BMI Gyro: 0x68 Expander: 0010000b = 0x10
Sanity LEDs
Decoupling Capacitors
